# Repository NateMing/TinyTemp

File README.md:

# TinyTemp - ATtiny85 Temperature Sensor

Temperature sensor project using ATtiny85 microcontroller with OLED display.

## Hardware
- ATtiny85 microcontroller
- SSD1306 OLED display
- MCP1700 voltage regulator
- Custom PCB design

## Files

### Code/
- `tinytemp.c` - Main temperature sensor code
- `tinyOLED.c/h` - OLED display driver
- `makefile` - Build configuration

### PCB Design
- `tinyTemp.kicad_*` - KiCAD project files
- `project2_N_Robinson_S_Chicoine.kicad_pcb` - Final PCB layout

### Custom Components
- `Symbols and Footprints/` - Custom KiCAD symbols and footprints
  - ATtiny85, SSD1306, MCP1700, capacitors, connectors

## Build
```bash
cd Code/
make
```

## Authors
Nathan Robinson & Sam Chicoine

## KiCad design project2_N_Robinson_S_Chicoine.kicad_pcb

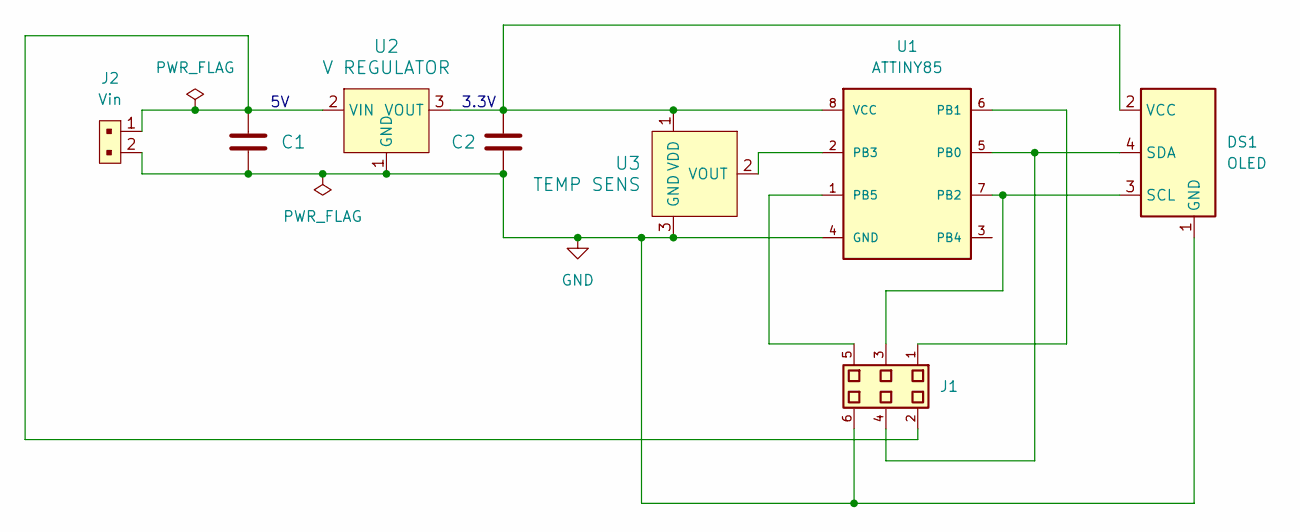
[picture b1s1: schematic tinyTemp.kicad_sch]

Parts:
C1: C320C104K5R5TA7317
C2: C330C105K5R5TA
DS1: OLED; SSD1306
J1: 30306-6002HB
J2: Vin; PinHeader_1x2_P2.54mm; MPN M20-9990246; Digi-Key_PN 952-2262-ND
U1: ATTINY85; ATTINY85-20PU; DigiKey_Part_Number ATTINY85-20PU-ND
U2: V REGULATOR; TO-92-3; MPN MCP1700-3302E/TO; Digi-Key_PN MCP1700-3302E/TO-ND
U3: TEMP SENS; TO-92-3; MPN TMP36GT9Z; Digi-Key_PN TMP36GT9Z-ND

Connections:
GND: C1.1, C2.1, DS1.1 (GND), J1.6, J2.2, U1.4 (GND), U2.1 (GND), U3.3 (GND)
unnamed: DS1.3 (SCL), J1.3, U1.7 (PB2)
unnamed: DS1.4 (SDA), J1.4, U1.5 (PB0)
unnamed: C2.2, DS1.2 (VCC), U1.8 (VCC), U2.3 (VOUT), U3.1 (VDD)
unnamed: J1.1, U1.6 (PB1)
unnamed: U1.2 (PB3), U3.2 (VOUT)
unnamed: J1.5, U1.1 (PB5)
unnamed: C1.2, J1.2, J2.1, U2.2 (VIN)

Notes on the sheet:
3.3V

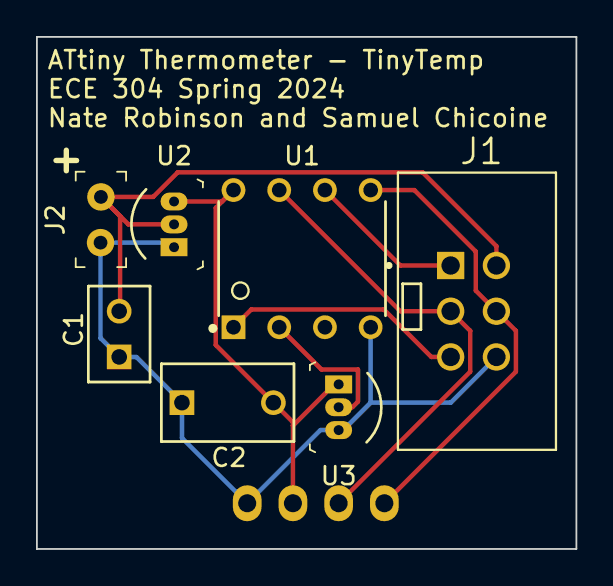
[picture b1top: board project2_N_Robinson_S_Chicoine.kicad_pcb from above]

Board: 2 copper layers, 30.0 x 28.4 mm, 8 parts (1 on the bottom side), 8 nets.

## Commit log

2025-09-02 Init
